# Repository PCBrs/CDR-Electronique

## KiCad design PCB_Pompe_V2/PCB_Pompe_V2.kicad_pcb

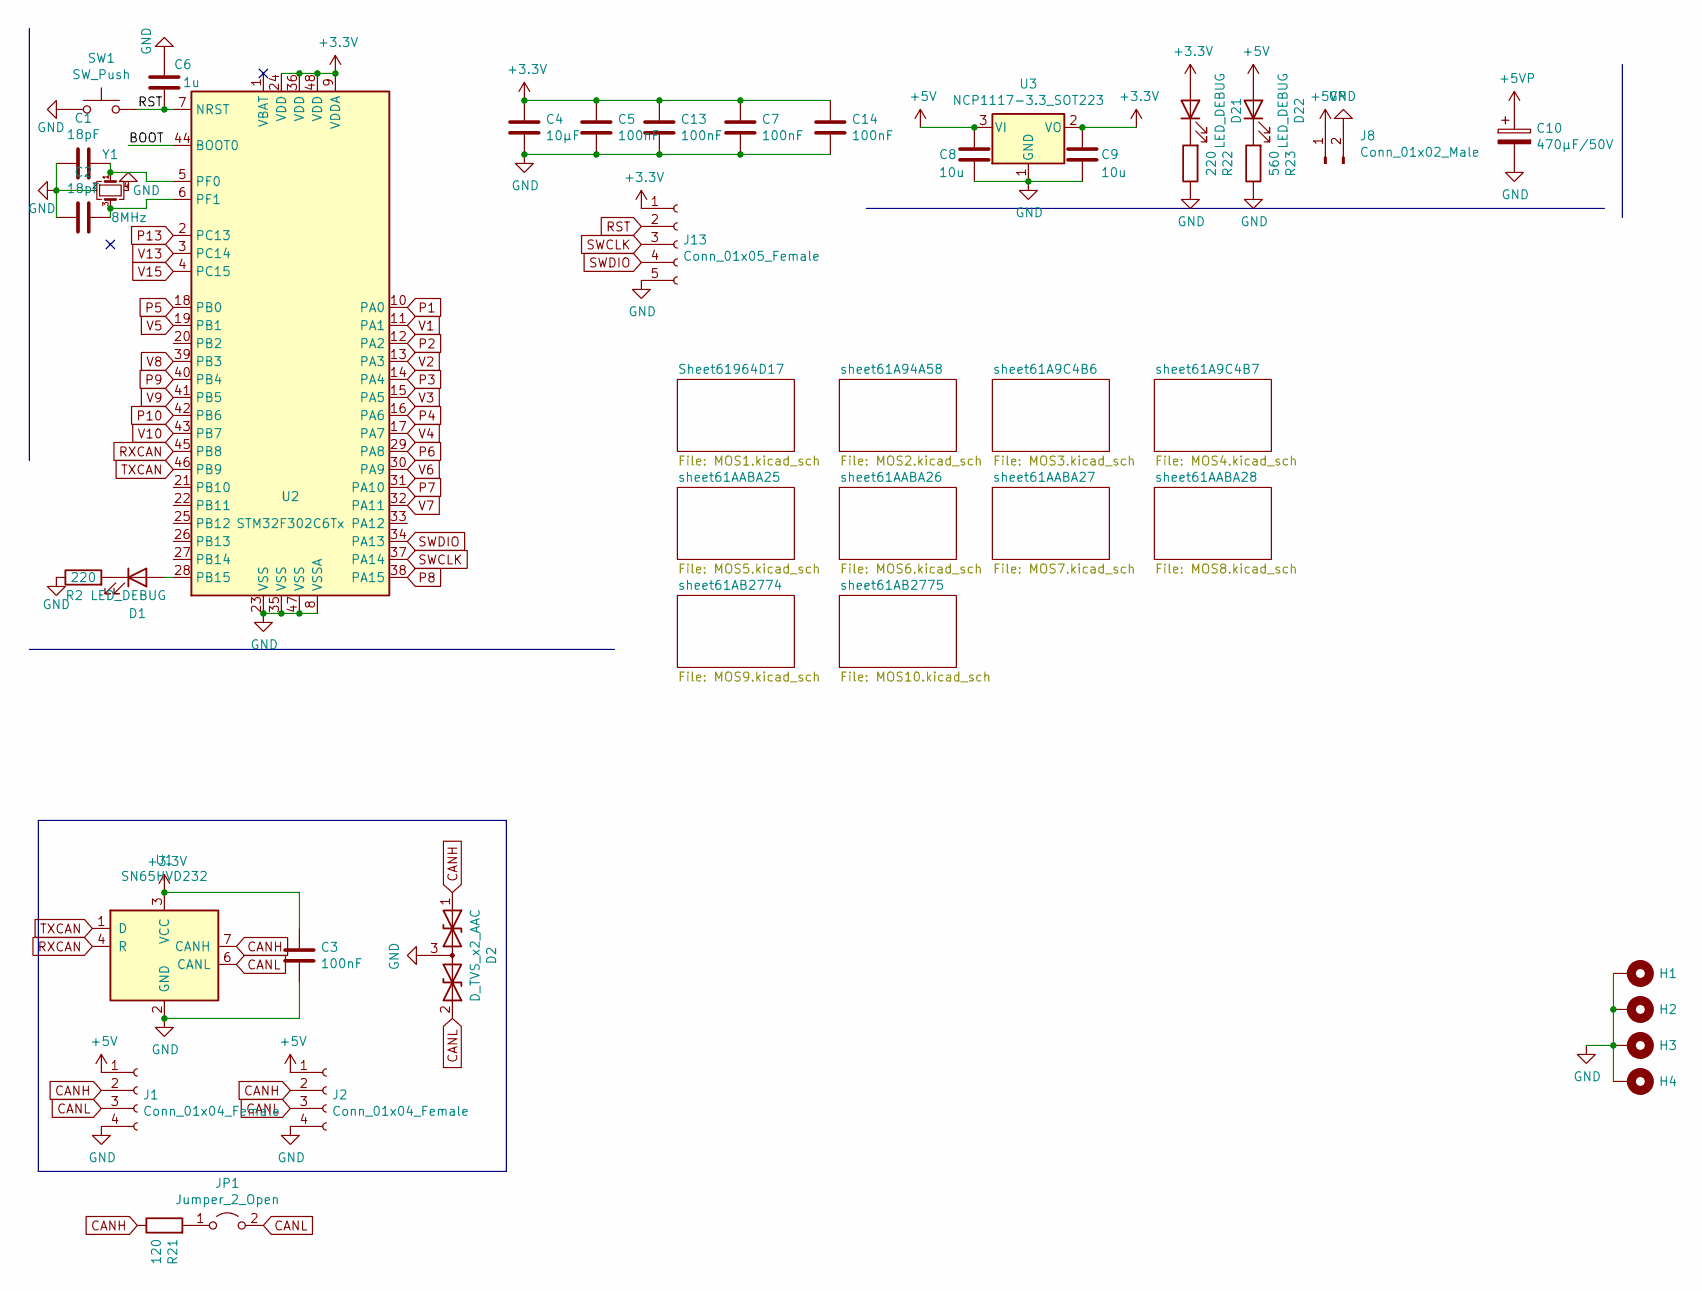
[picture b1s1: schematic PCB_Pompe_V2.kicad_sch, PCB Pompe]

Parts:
C1, C2: 18pF; C_0805_2012Metric_Pad1.18x1.45mm_HandSolder
C3, C5, C7, C13, C14: 100nF; C_0805_2012Metric_Pad1.18x1.45mm_HandSolder
C4: 10µF; C_0805_2012Metric_Pad1.18x1.45mm_HandSolder
C6: 1u; C_0805_2012Metric_Pad1.18x1.45mm_HandSolder
C8, C9: 10u; C_0805_2012Metric_Pad1.18x1.45mm_HandSolder
C10: 470µF/50V; CP_Radial_D10.0mm_P5.00mm
D1, D21, D22: LED_DEBUG; LED_0805_2012Metric_Pad1.15x1.40mm_HandSolder
D2: D_TVS_x2_AAC; SOT-23
H1, H2, H3, H4: MountingHole_Pad; MountingHole_3.2mm_M3_Pad_Via
J1, J2: Conn_01x04_Female; 690367290476
J8: Conn_01x02_Male; Wuerth_3.96mm_2pin_645002114822
J13: Conn_01x05_Female; PinSocket_1x05_P2.54mm_Vertical
JP1: Jumper_2_Open; PinHeader_1x02_P2.54mm_Vertical
R2, R22: 220; R_0805_2012Metric_Pad1.20x1.40mm_HandSolder
R21: 120; R_0805_2012Metric_Pad1.20x1.40mm_HandSolder
R23: 560; R_0805_2012Metric_Pad1.20x1.40mm_HandSolder
SW1: SW_Push; SW_SPST_FSMSM
U1: SN65HVD232; SOIC-8_3.9x4.9mm_P1.27mm
U2: STM32F302C6Tx; LQFP-48_7x7mm_P0.5mm
U3: NCP1117-3.3_SOT223; SOT-223-3_TabPin2
Y1: 8MHz; Crystal_SMD_5032-4Pin_5.0x3.2mm

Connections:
+3V3: C3.2, C4.2, C5.2, C7.2, C9.2, C13.2, C14.2, D21.2 (A), J13.1, U1.3 (VCC), U2.9 (VDDA), U2.24 (VDD), U2.36 (VDD), U2.48 (VDD), U3.2 (VO)
+5V: C8.2, D22.2 (A), J1.1, J2.1, U3.3 (VI)
+5VP: C10.1, J8.1; also elsewhere on the board
CANH: D2.1 (A1), J1.2, J2.2, R21.1, U1.7 (CANH)
CANL: D2.2 (A2), J1.3, J2.3, JP1.2 (B), U1.6 (CANL)
GND: C1.2, C2.2, C3.1, C4.1, C5.1, C6.2, C7.1, C8.1, C9.1, C10.2, C13.1, C14.1, D2.3 (common), H1.1, H2.1, H3.1, H4.1, J1.4, J2.4, J8.2, J13.5, R2.1, R22.1, R23.1, SW1.1, U1.2 (GND), U2.8 (VSSA), U2.23 (VSS), U2.35 (VSS), U2.47 (VSS), U3.1 (GND), Y1.2, Y1.4; also elsewhere on the board
unnamed: C1.1, U2.5 (PF0), Y1.1
unnamed: C2.1, U2.6 (PF1), Y1.3
unnamed: D1.1 (K), R2.2
unnamed: D1.2 (A), U2.28 (PB15)
unnamed: D21.1 (K), R22.2
unnamed: D22.1 (K), R23.2
unnamed: JP1.1 (A), R21.2
P1: U2.10 (PA0); also elsewhere on the board
P2: U2.12 (PA2); also elsewhere on the board
P3: U2.14 (PA4); also elsewhere on the board
P4: U2.16 (PA6); also elsewhere on the board
P5: U2.18 (PB0); also elsewhere on the board
P6: U2.29 (PA8); also elsewhere on the board
P7: U2.31 (PA10); also elsewhere on the board
P8: U2.38 (PA15); also elsewhere on the board
P9: U2.40 (PB4); also elsewhere on the board
P10: U2.42 (PB6); also elsewhere on the board
RST: C6.1, J13.2, SW1.2, U2.7 (NRST)
RXCAN: U1.4 (R), U2.45 (PB8)
SWCLK: J13.3, U2.37 (PA14)
SWDIO: J13.4, U2.34 (PA13)
TXCAN: U1.1 (D), U2.46 (PB9)
V1: U2.11 (PA1); also elsewhere on the board
V2: U2.13 (PA3); also elsewhere on the board
V3: U2.15 (PA5); also elsewhere on the board
V4: U2.17 (PA7); also elsewhere on the board
V5: U2.19 (PB1); also elsewhere on the board
V6: U2.30 (PA9); also elsewhere on the board
V7: U2.32 (PA11); also elsewhere on the board
V8: U2.39 (PB3); also elsewhere on the board
V9: U2.41 (PB5); also elsewhere on the board
V10: U2.43 (PB7); also elsewhere on the board

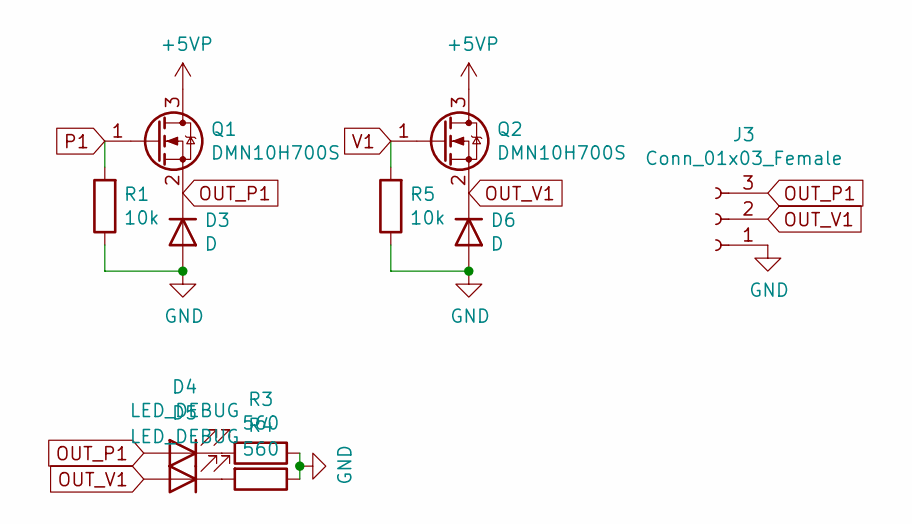
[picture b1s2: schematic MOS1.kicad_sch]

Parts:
D3, D6: D; D_SOD-123
D4, D5: LED_DEBUG; LED_0805_2012Metric_Pad1.15x1.40mm_HandSolder
J3: Conn_01x03_Female; Wuerth_2.54mm_3pins_61900311121
Q1, Q2: DMN10H700S; SOT-23
R1, R5: 10k; R_0805_2012Metric_Pad1.20x1.40mm_HandSolder
R3, R4: 560; R_0805_2012Metric_Pad1.20x1.40mm_HandSolder

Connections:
+5VP: Q1.3 (D), Q2.3 (D); also elsewhere on the board
GND: D3.2 (A), D6.2 (A), J3.1, R1.1, R3.1, R4.1, R5.1; also elsewhere on the board
unnamed: D4.1 (K), R3.2
unnamed: D5.1 (K), R4.2
OUT_P1: D3.1 (K), D4.2 (A), J3.3, Q1.2 (S)
OUT_V1: D5.2 (A), D6.1 (K), J3.2, Q2.2 (S)
P1: Q1.1 (G), R1.2; also elsewhere on the board
V1: Q2.1 (G), R5.2; also elsewhere on the board

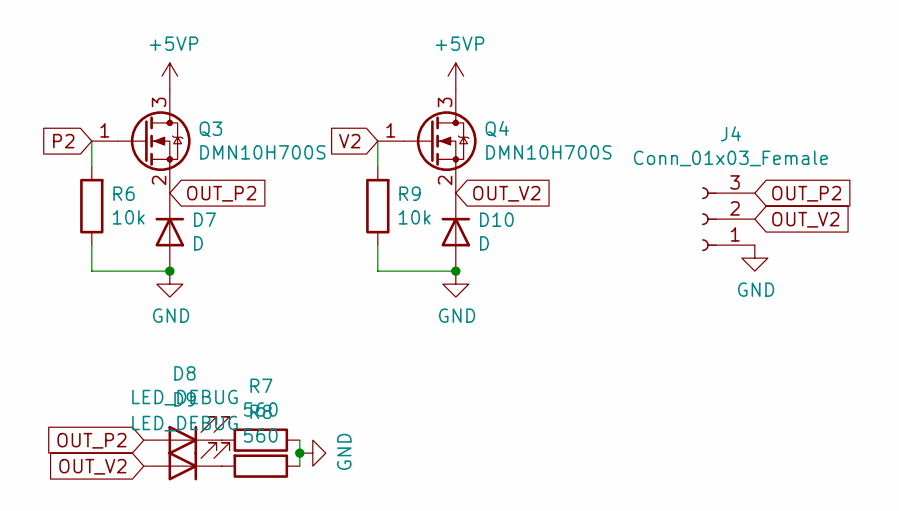
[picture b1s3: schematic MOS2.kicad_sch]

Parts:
D7, D10: D; D_SOD-123
D8, D9: LED_DEBUG; LED_0805_2012Metric_Pad1.15x1.40mm_HandSolder
J4: Conn_01x03_Female; Wuerth_2.54mm_3pins_61900311121
Q3, Q4: DMN10H700S; SOT-23
R6, R9: 10k; R_0805_2012Metric_Pad1.20x1.40mm_HandSolder
R7, R8: 560; R_0805_2012Metric_Pad1.20x1.40mm_HandSolder

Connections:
+5VP: Q3.3 (D), Q4.3 (D); also elsewhere on the board
GND: D7.2 (A), D10.2 (A), J4.1, R6.1, R7.1, R8.1, R9.1; also elsewhere on the board
unnamed: D8.1 (K), R7.2
unnamed: D9.1 (K), R8.2
OUT_P2: D7.1 (K), D8.2 (A), J4.3, Q3.2 (S)
OUT_V2: D9.2 (A), D10.1 (K), J4.2, Q4.2 (S)
P2: Q3.1 (G), R6.2; also elsewhere on the board
V2: Q4.1 (G), R9.2; also elsewhere on the board

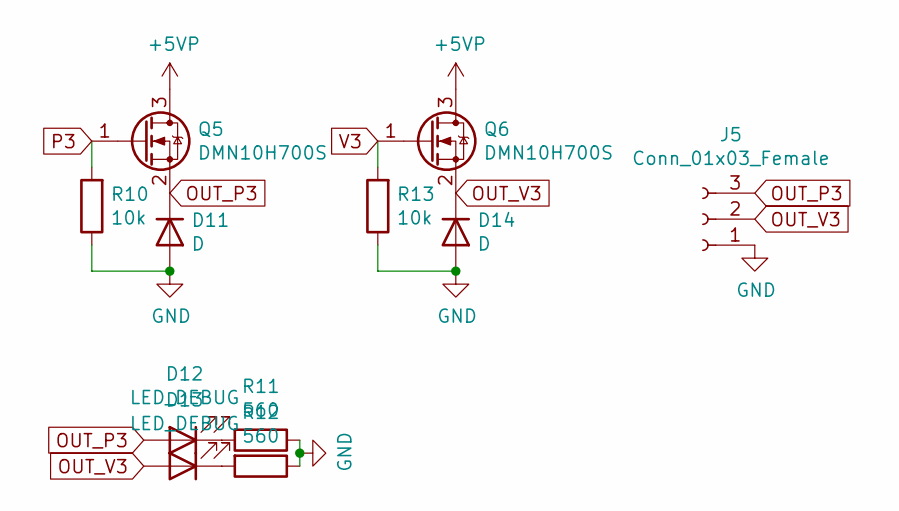
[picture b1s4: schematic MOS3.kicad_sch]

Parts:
D11, D14: D; D_SOD-123
D12, D13: LED_DEBUG; LED_0805_2012Metric_Pad1.15x1.40mm_HandSolder
J5: Conn_01x03_Female; Wuerth_2.54mm_3pins_61900311121
Q5, Q6: DMN10H700S; SOT-23
R10, R13: 10k; R_0805_2012Metric_Pad1.20x1.40mm_HandSolder
R11, R12: 560; R_0805_2012Metric_Pad1.20x1.40mm_HandSolder

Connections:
+5VP: Q5.3 (D), Q6.3 (D); also elsewhere on the board
GND: D11.2 (A), D14.2 (A), J5.1, R10.1, R11.1, R12.1, R13.1; also elsewhere on the board
unnamed: D12.1 (K), R11.2
unnamed: D13.1 (K), R12.2
OUT_P3: D11.1 (K), D12.2 (A), J5.3, Q5.2 (S)
OUT_V3: D13.2 (A), D14.1 (K), J5.2, Q6.2 (S)
P3: Q5.1 (G), R10.2; also elsewhere on the board
V3: Q6.1 (G), R13.2; also elsewhere on the board

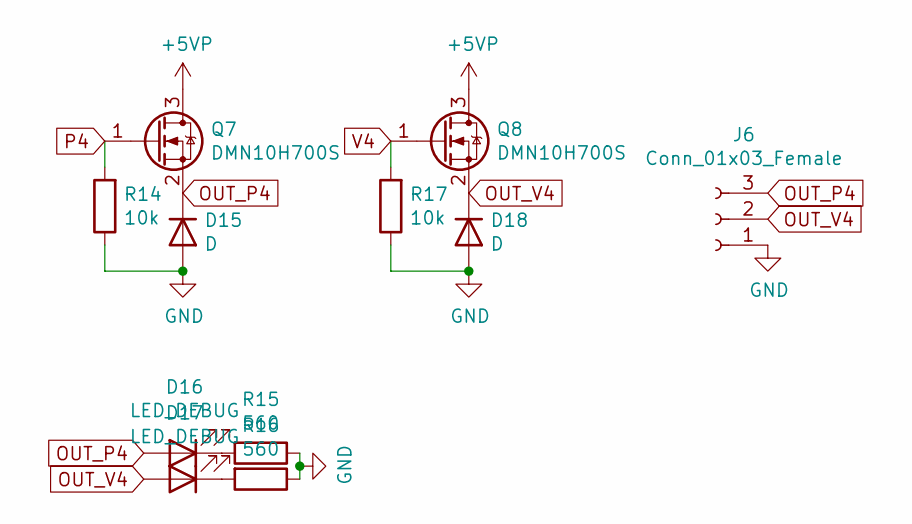
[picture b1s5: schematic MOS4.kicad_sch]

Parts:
D15, D18: D; D_SOD-123
D16, D17: LED_DEBUG; LED_0805_2012Metric_Pad1.15x1.40mm_HandSolder
J6: Conn_01x03_Female; Wuerth_2.54mm_3pins_61900311121
Q7, Q8: DMN10H700S; SOT-23
R14, R17: 10k; R_0805_2012Metric_Pad1.20x1.40mm_HandSolder
R15, R16: 560; R_0805_2012Metric_Pad1.20x1.40mm_HandSolder

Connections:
+5VP: Q7.3 (D), Q8.3 (D); also elsewhere on the board
GND: D15.2 (A), D18.2 (A), J6.1, R14.1, R15.1, R16.1, R17.1; also elsewhere on the board
unnamed: D16.1 (K), R15.2
unnamed: D17.1 (K), R16.2
OUT_P4: D15.1 (K), D16.2 (A), J6.3, Q7.2 (S)
OUT_V4: D17.2 (A), D18.1 (K), J6.2, Q8.2 (S)
P4: Q7.1 (G), R14.2; also elsewhere on the board
V4: Q8.1 (G), R17.2; also elsewhere on the board

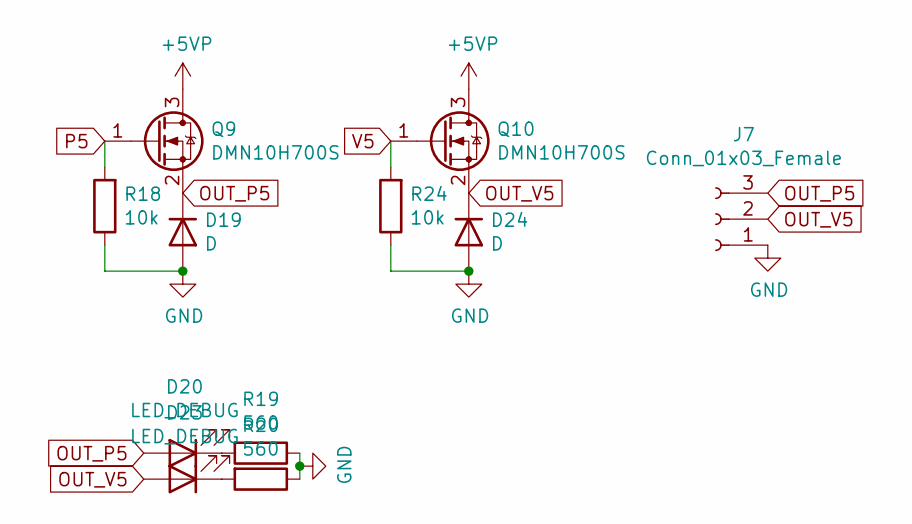
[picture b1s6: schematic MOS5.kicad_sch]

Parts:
D19, D24: D; D_SOD-123
D20, D23: LED_DEBUG; LED_0805_2012Metric_Pad1.15x1.40mm_HandSolder
J7: Conn_01x03_Female; Wuerth_2.54mm_3pins_61900311121
Q9, Q10: DMN10H700S; SOT-23
R18, R24: 10k; R_0805_2012Metric_Pad1.20x1.40mm_HandSolder
R19, R20: 560; R_0805_2012Metric_Pad1.20x1.40mm_HandSolder

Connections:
+5VP: Q9.3 (D), Q10.3 (D); also elsewhere on the board
GND: D19.2 (A), D24.2 (A), J7.1, R18.1, R19.1, R20.1, R24.1; also elsewhere on the board
unnamed: D20.1 (K), R19.2
unnamed: D23.1 (K), R20.2
OUT_P5: D19.1 (K), D20.2 (A), J7.3, Q9.2 (S)
OUT_V5: D23.2 (A), D24.1 (K), J7.2, Q10.2 (S)
P5: Q9.1 (G), R18.2; also elsewhere on the board
V5: Q10.1 (G), R24.2; also elsewhere on the board

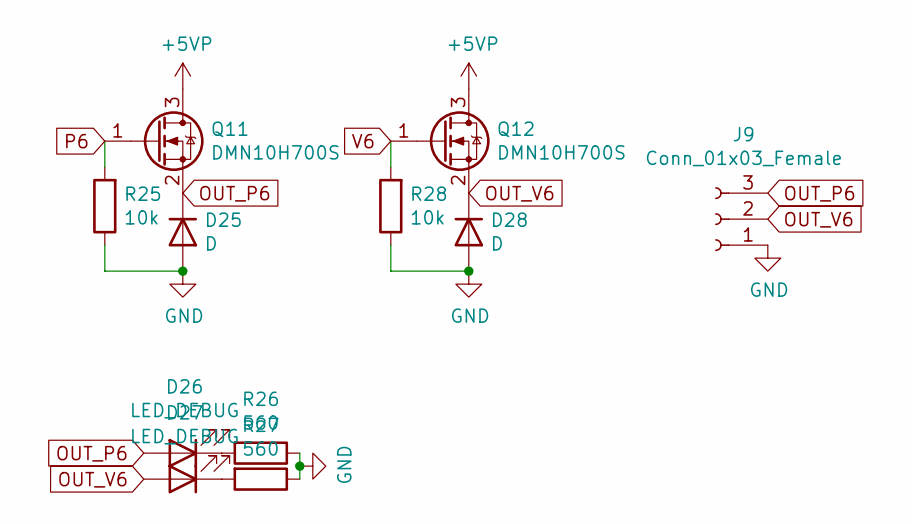
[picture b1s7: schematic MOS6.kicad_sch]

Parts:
D25, D28: D; D_SOD-123
D26, D27: LED_DEBUG; LED_0805_2012Metric_Pad1.15x1.40mm_HandSolder
J9: Conn_01x03_Female; Wuerth_2.54mm_3pins_61900311121
Q11, Q12: DMN10H700S; SOT-23
R25, R28: 10k; R_0805_2012Metric_Pad1.20x1.40mm_HandSolder
R26, R27: 560; R_0805_2012Metric_Pad1.20x1.40mm_HandSolder

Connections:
+5VP: Q11.3 (D), Q12.3 (D); also elsewhere on the board
GND: D25.2 (A), D28.2 (A), J9.1, R25.1, R26.1, R27.1, R28.1; also elsewhere on the board
unnamed: D26.1 (K), R26.2
unnamed: D27.1 (K), R27.2
OUT_P6: D25.1 (K), D26.2 (A), J9.3, Q11.2 (S)
OUT_V6: D27.2 (A), D28.1 (K), J9.2, Q12.2 (S)
P6: Q11.1 (G), R25.2; also elsewhere on the board
V6: Q12.1 (G), R28.2; also elsewhere on the board

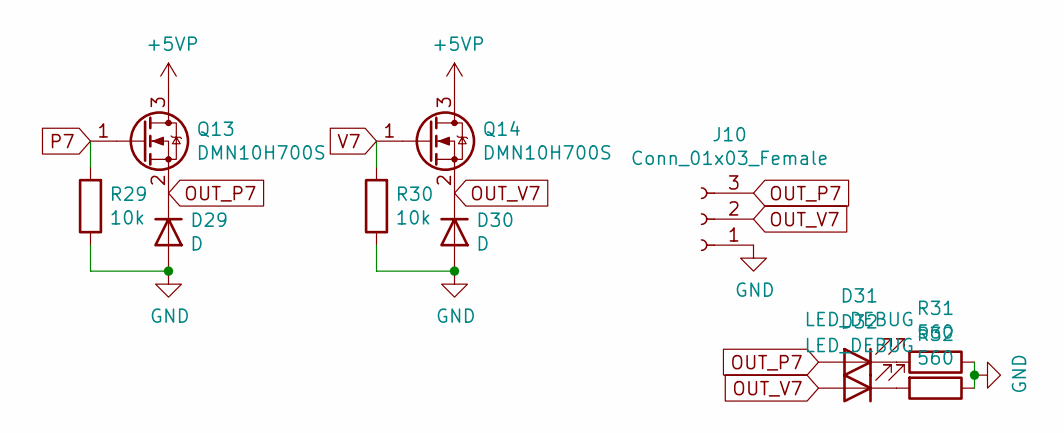
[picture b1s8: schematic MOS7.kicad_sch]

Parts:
D29, D30: D; D_SOD-123
D31, D32: LED_DEBUG; LED_0805_2012Metric_Pad1.15x1.40mm_HandSolder
J10: Conn_01x03_Female; Wuerth_2.54mm_3pins_61900311121
Q13, Q14: DMN10H700S; SOT-23
R29, R30: 10k; R_0805_2012Metric_Pad1.20x1.40mm_HandSolder
R31, R32: 560; R_0805_2012Metric_Pad1.20x1.40mm_HandSolder

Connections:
+5VP: Q13.3 (D), Q14.3 (D); also elsewhere on the board
GND: D29.2 (A), D30.2 (A), J10.1, R29.1, R30.1, R31.1, R32.1; also elsewhere on the board
unnamed: D31.1 (K), R31.2
unnamed: D32.1 (K), R32.2
OUT_P7: D29.1 (K), D31.2 (A), J10.3, Q13.2 (S)
OUT_V7: D30.1 (K), D32.2 (A), J10.2, Q14.2 (S)
P7: Q13.1 (G), R29.2; also elsewhere on the board
V7: Q14.1 (G), R30.2; also elsewhere on the board

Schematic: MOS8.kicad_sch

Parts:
D33, D36: D; D_SOD-123
D34, D35: LED_DEBUG; LED_0805_2012Metric_Pad1.15x1.40mm_HandSolder
J11: Conn_01x03_Female; Wuerth_2.54mm_3pins_61900311121
Q15, Q16: DMN10H700S; SOT-23
R33, R36: 10k; R_0805_2012Metric_Pad1.20x1.40mm_HandSolder
R34, R35: 560; R_0805_2012Metric_Pad1.20x1.40mm_HandSolder

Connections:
+5VP: Q15.3 (D), Q16.3 (D); also elsewhere on the board
GND: D33.2 (A), D36.2 (A), J11.1, R33.1, R34.1, R35.1, R36.1; also elsewhere on the board
unnamed: D34.1 (K), R34.2
unnamed: D35.1 (K), R35.2
OUT_P8: D33.1 (K), D34.2 (A), J11.3, Q15.2 (S)
OUT_V8: D35.2 (A), D36.1 (K), J11.2, Q16.2 (S)
P8: Q15.1 (G), R33.2; also elsewhere on the board
V8: Q16.1 (G), R36.2; also elsewhere on the board

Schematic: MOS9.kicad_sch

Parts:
D37, D40: D; D_SOD-123
D38, D39: LED_DEBUG; LED_0805_2012Metric_Pad1.15x1.40mm_HandSolder
J12: Conn_01x03_Female; Wuerth_2.54mm_3pins_61900311121
Q17, Q18: DMN10H700S; SOT-23
R37, R40: 10k; R_0805_2012Metric_Pad1.20x1.40mm_HandSolder
R38, R39: 560; R_0805_2012Metric_Pad1.20x1.40mm_HandSolder

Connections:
+5VP: Q17.3 (D), Q18.3 (D); also elsewhere on the board
GND: D37.2 (A), D40.2 (A), J12.1, R37.1, R38.1, R39.1, R40.1; also elsewhere on the board
unnamed: D38.1 (K), R38.2
unnamed: D39.1 (K), R39.2
OUT_P9: D37.1 (K), D38.2 (A), J12.3, Q17.2 (S)
OUT_V9: D39.2 (A), D40.1 (K), J12.2, Q18.2 (S)
P9: Q17.1 (G), R37.2; also elsewhere on the board
V9: Q18.1 (G), R40.2; also elsewhere on the board

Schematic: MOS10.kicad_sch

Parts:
D41, D44: D; D_SOD-123
D42, D43: LED_DEBUG; LED_0805_2012Metric_Pad1.15x1.40mm_HandSolder
J14: Conn_01x03_Female; Wuerth_2.54mm_3pins_61900311121
Q19, Q20: DMN10H700S; SOT-23
R41, R44: 10k; R_0805_2012Metric_Pad1.20x1.40mm_HandSolder
R42, R43: 560; R_0805_2012Metric_Pad1.20x1.40mm_HandSolder

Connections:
+5VP: Q19.3 (D), Q20.3 (D); also elsewhere on the board
GND: D41.2 (A), D44.2 (A), J14.1, R41.1, R42.1, R43.1, R44.1; also elsewhere on the board
unnamed: D42.1 (K), R42.2
unnamed: D43.1 (K), R43.2
OUT_P10: D41.1 (K), D42.2 (A), J14.3, Q19.2 (S)
OUT_V10: D43.2 (A), D44.1 (K), J14.2, Q20.2 (S)
P10: Q19.1 (G), R41.2; also elsewhere on the board
V10: Q20.1 (G), R44.2; also elsewhere on the board

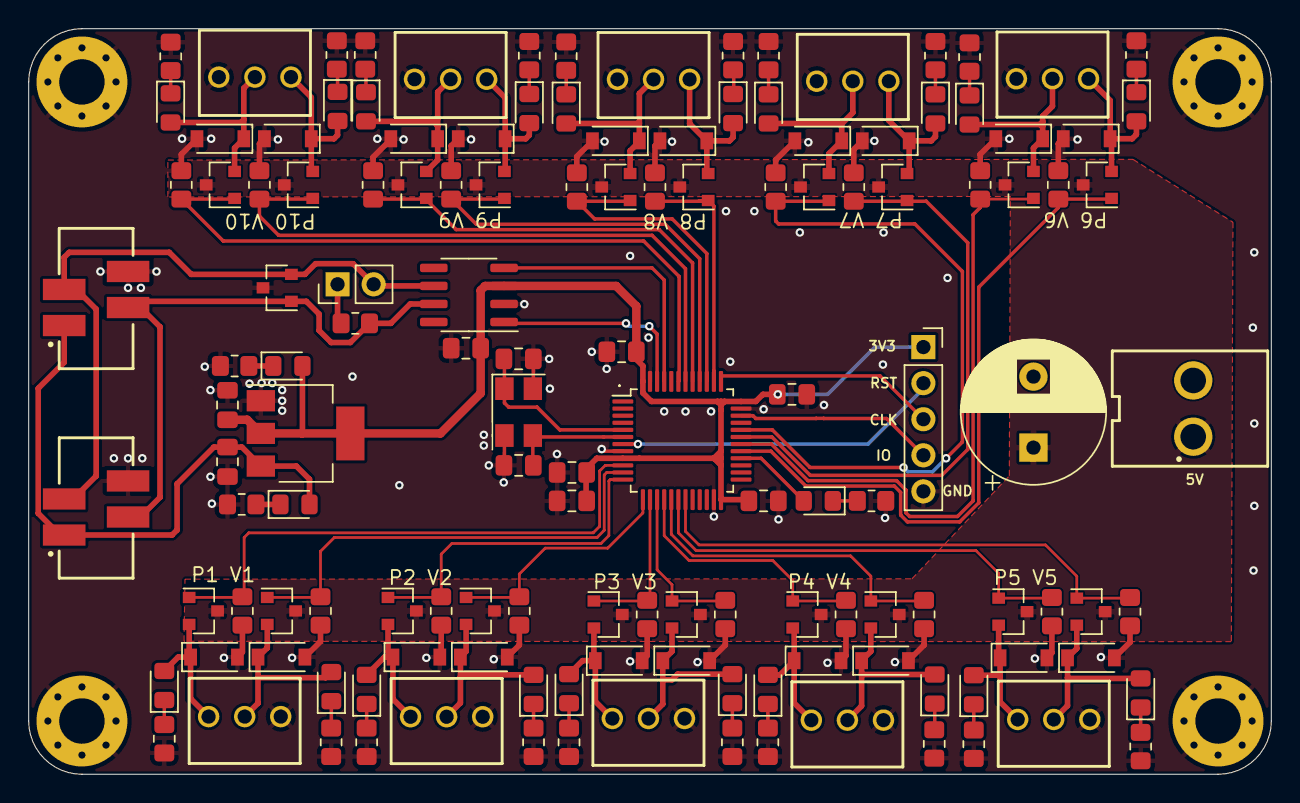
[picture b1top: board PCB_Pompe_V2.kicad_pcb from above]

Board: 2 copper layers, 87.5 x 52.5 mm, 142 parts (0 on the bottom side), 78 nets.

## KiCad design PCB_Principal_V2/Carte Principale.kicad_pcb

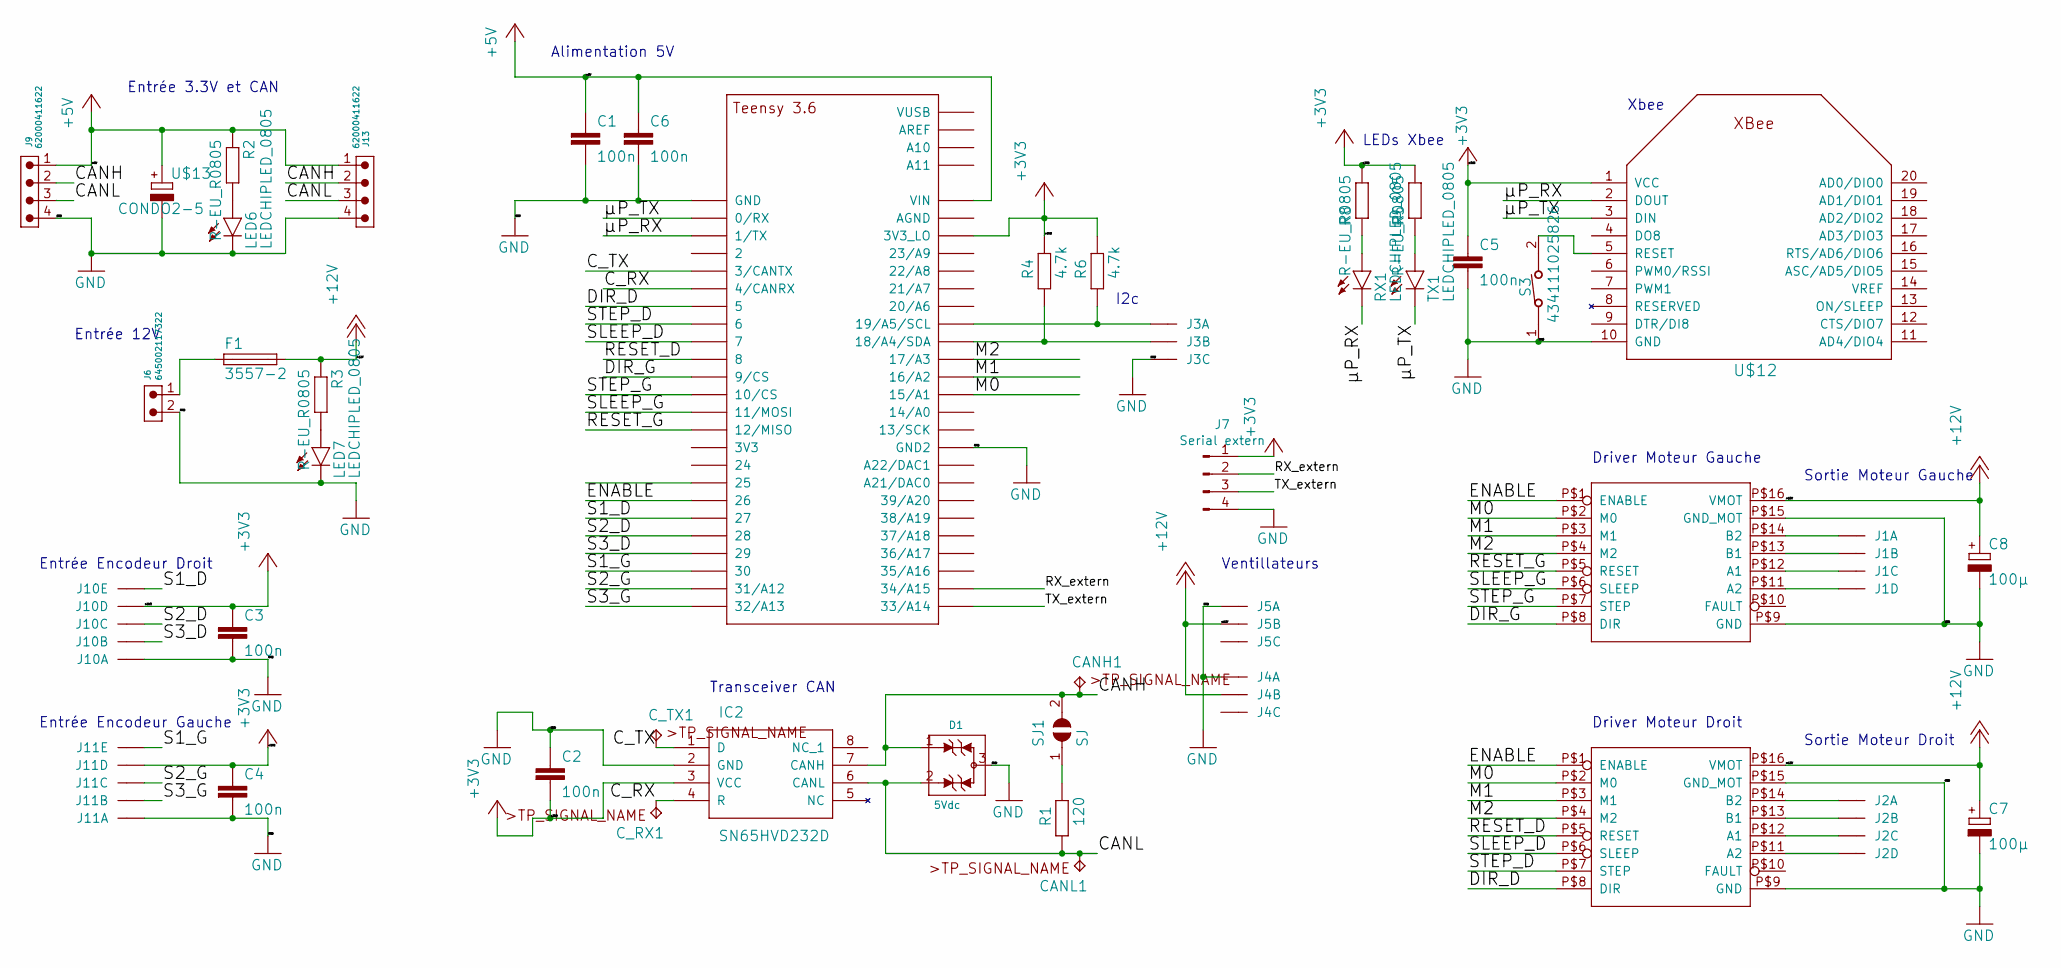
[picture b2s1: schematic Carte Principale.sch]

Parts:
C1, C2, C3, C4, C5, C6: 100n; C0805; MPN DT000363
C7, C8: 100µ; E2,5-7
CANH1: TPB1,27; B1,27
CANL1: TPB1,27; B1,27
C_RX1: TPB1,27; B1,27
C_TX1: TPB1,27; B1,27
D1: 5Vdc; WE-TVS_SOT23-3L
F1: 3557-2; FUSE_3557-2
IC2: SN65HVD232D; SOIC127P600X175-8N
J1, J2: MOLEX_4DROIT; CON_4_DROIT
J3, J4, J5: MOLEX_3DROIT; CON_3_DROIT
J6: 645002117322
J7: Serial extern; PinHeader_1x04_P2.54mm_Vertical
J9, J13: 62000411622
J10, J11: 22-?-0527-2051; 6410-05
LED6, LED7: LEDCHIPLED_0805; CHIPLED_0805
R1: 120; R0805
R2, R3, R5, R8: R-EU_R0805; R0805
R4, R6: 4.7k; R0805
RX1: LEDCHIPLED_0805; CHIPLED_0805
S3: 434111025826
SJ1: SJ
TX1: LEDCHIPLED_0805; CHIPLED_0805
U$1, U$2: DRV8825
U$5: TEENSY_3.5_3.6_BASIC
U$12: XBEE
U$13: CONDO2-5; E2-5

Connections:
+3V3: C2.2, C3.1, C4.1, C5.1, IC2.3 (VCC), J7.1, J10.4, J11.4, R4.2, R5.1, R6.2, R8.1, U$5.3V3_LO, U$12.1 (VCC)
+5V: C1.1, C6.1, J9.1, J13.1, R2.1, U$5.VIN, U$13.+
+12V: C7.+, C8.+, F1.3 (2), F1.4 (2), J4.2, J5.2, R3.1, U$1.P$16 (VMOT), U$2.P$16 (VMOT)
/CANH: CANH1.TP, D1.1 (I/O1), IC2.7 (CANH), J9.2, J13.2, SJ1.2
/CANL: CANL1.TP, D1.2 (I/O2), IC2.6 (CANL), J9.3, J13.3, R1.1
/C_RX: C_RX1.TP, IC2.4 (R), U$5.4/CANRX
/C_TX: C_TX1.TP, IC2.1 (D), U$5.3/CANTX
/DIR_D: U$2.P$8 (DIR), U$5.5
/DIR_G: U$1.P$8 (DIR), U$5.9/CS
/ENABLE: U$1.P$1 (ENABLE), U$2.P$1 (ENABLE), U$5.26
/M0: U$1.P$2 (M0), U$2.P$2 (M0), U$5.15/A1
/M1: U$1.P$3 (M1), U$2.P$3 (M1), U$5.16/A2
/M2: U$1.P$4 (M2), U$2.P$4 (M2), U$5.17/A3
/RESET_D: U$2.P$5 (RESET), U$5.8
/RESET_G: U$1.P$5 (RESET), U$5.12/MISO
/RX_extern: J7.2, U$5.34/A15
/S1_D: J10.5, U$5.27
/S1_G: J11.5, U$5.30
/S2_D: J10.3, U$5.28
/S2_G: J11.3, U$5.31/A12
/S3_D: J10.2, U$5.29
/S3_G: J11.2, U$5.32/A13
/SLEEP_D: U$2.P$6 (SLEEP), U$5.7
/SLEEP_G: U$1.P$6 (SLEEP), U$5.11/MOSI
/STEP_D: U$2.P$7 (STEP), U$5.6
/STEP_G: U$1.P$7 (STEP), U$5.10/CS
/TX_extern: J7.3, U$5.33/A14
/µP_RX: RX1.C, U$5.1/TX, U$12.2 (DOUT)
/µP_TX: TX1.C, U$5.0/RX, U$12.3 (DIN)
GND: C1.2, C2.1, C3.2, C4.2, C5.2, C6.2, C7.-, C8.-, D1.3 (GND), IC2.2 (GND), J3.3, J4.1, J5.1, J6.2, J7.4, J9.4, J10.1, J11.1, J13.4, LED6.C, LED7.C, S3.1, U$1.P$9 (GND), U$1.P$15 (GND_MOT), U$2.P$9 (GND), U$2.P$15 (GND_MOT), U$5.GND, U$5.GND2, U$12.10 (GND), U$13.-
unnamed: F1.1, F1.2 (1), J6.1
unnamed: J1.1, U$1.P$14 (B2)
unnamed: J1.2, U$1.P$13 (B1)
unnamed: J1.3, U$1.P$12 (A1)
unnamed: J1.4, U$1.P$11 (A2)
unnamed: J2.1, U$2.P$14 (B2)
unnamed: J2.2, U$2.P$13 (B1)
unnamed: J2.3, U$2.P$12 (A1)
unnamed: J2.4, U$2.P$11 (A2)
unnamed: J3.1, R6.1, U$5.19/A5/SCL
unnamed: J3.2, R4.1, U$5.18/A4/SDA
unnamed: LED6.A, R2.2
unnamed: LED7.A, R3.2
unnamed: R1.2, SJ1.1
unnamed: R5.2, TX1.A
unnamed: R8.2, RX1.A
unnamed: S3.2, U$12.5 (RESET)

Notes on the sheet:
Entrée Encodeur Gauche
Entrée Encodeur Droit
Sortie Moteur Gauche
Sortie Moteur Droit
Xbee
Driver Moteur Gauche
Driver Moteur Droit
Transceiver CAN
Entrée 12V
Entrée 3.3V et CAN
LEDs Xbee
I2c
Ventillateurs
Alimentation 5V

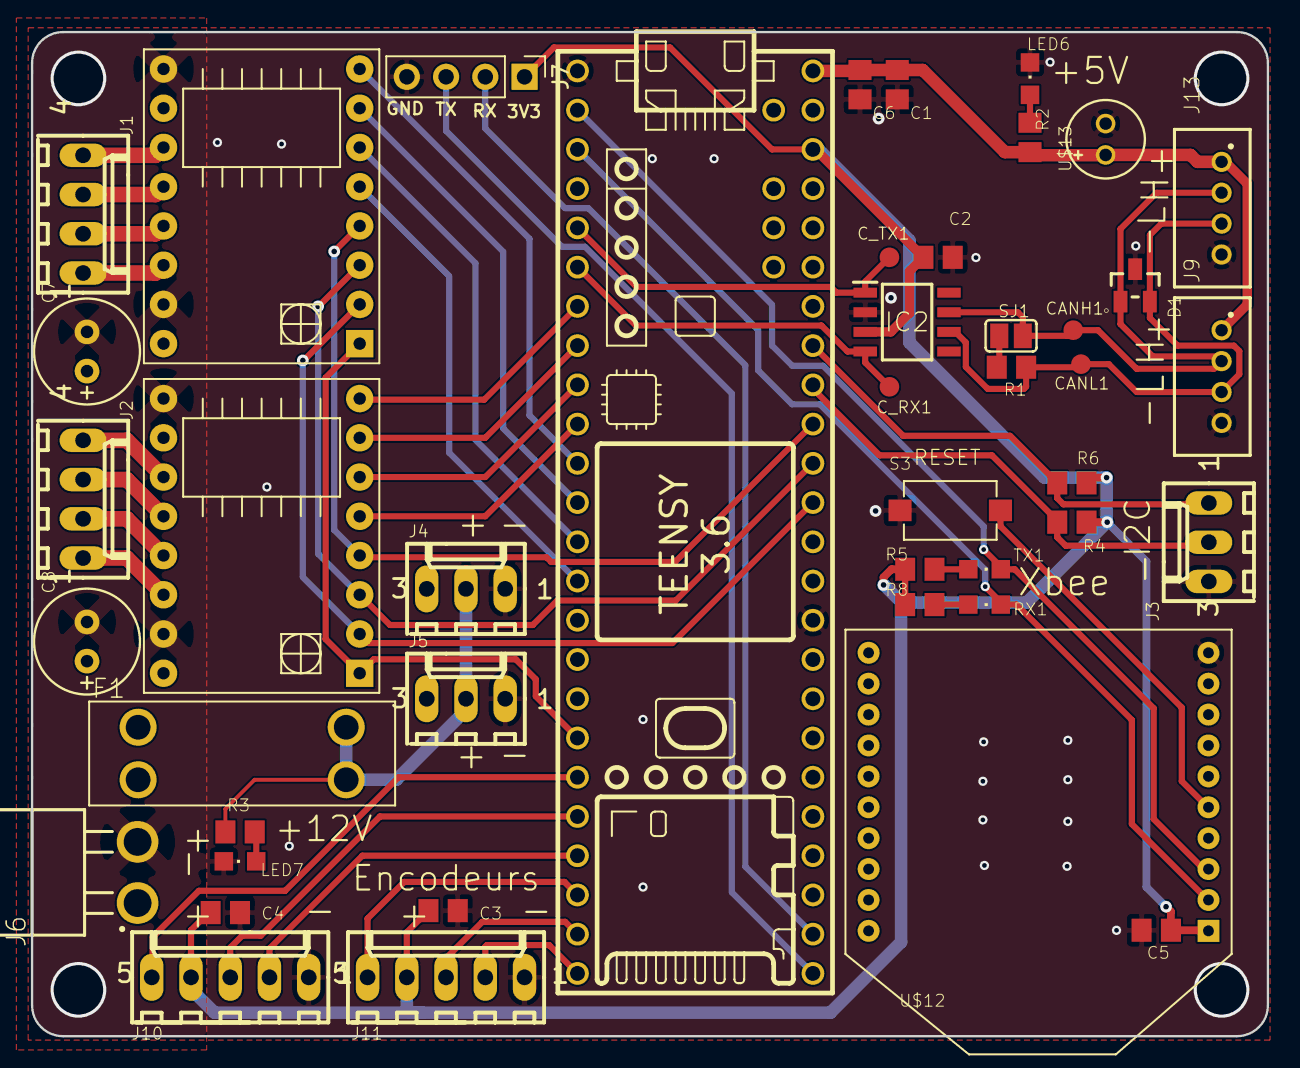
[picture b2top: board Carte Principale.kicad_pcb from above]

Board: 2 copper layers, 80.0 x 65.0 mm, 44 parts (0 on the bottom side), 47 nets.

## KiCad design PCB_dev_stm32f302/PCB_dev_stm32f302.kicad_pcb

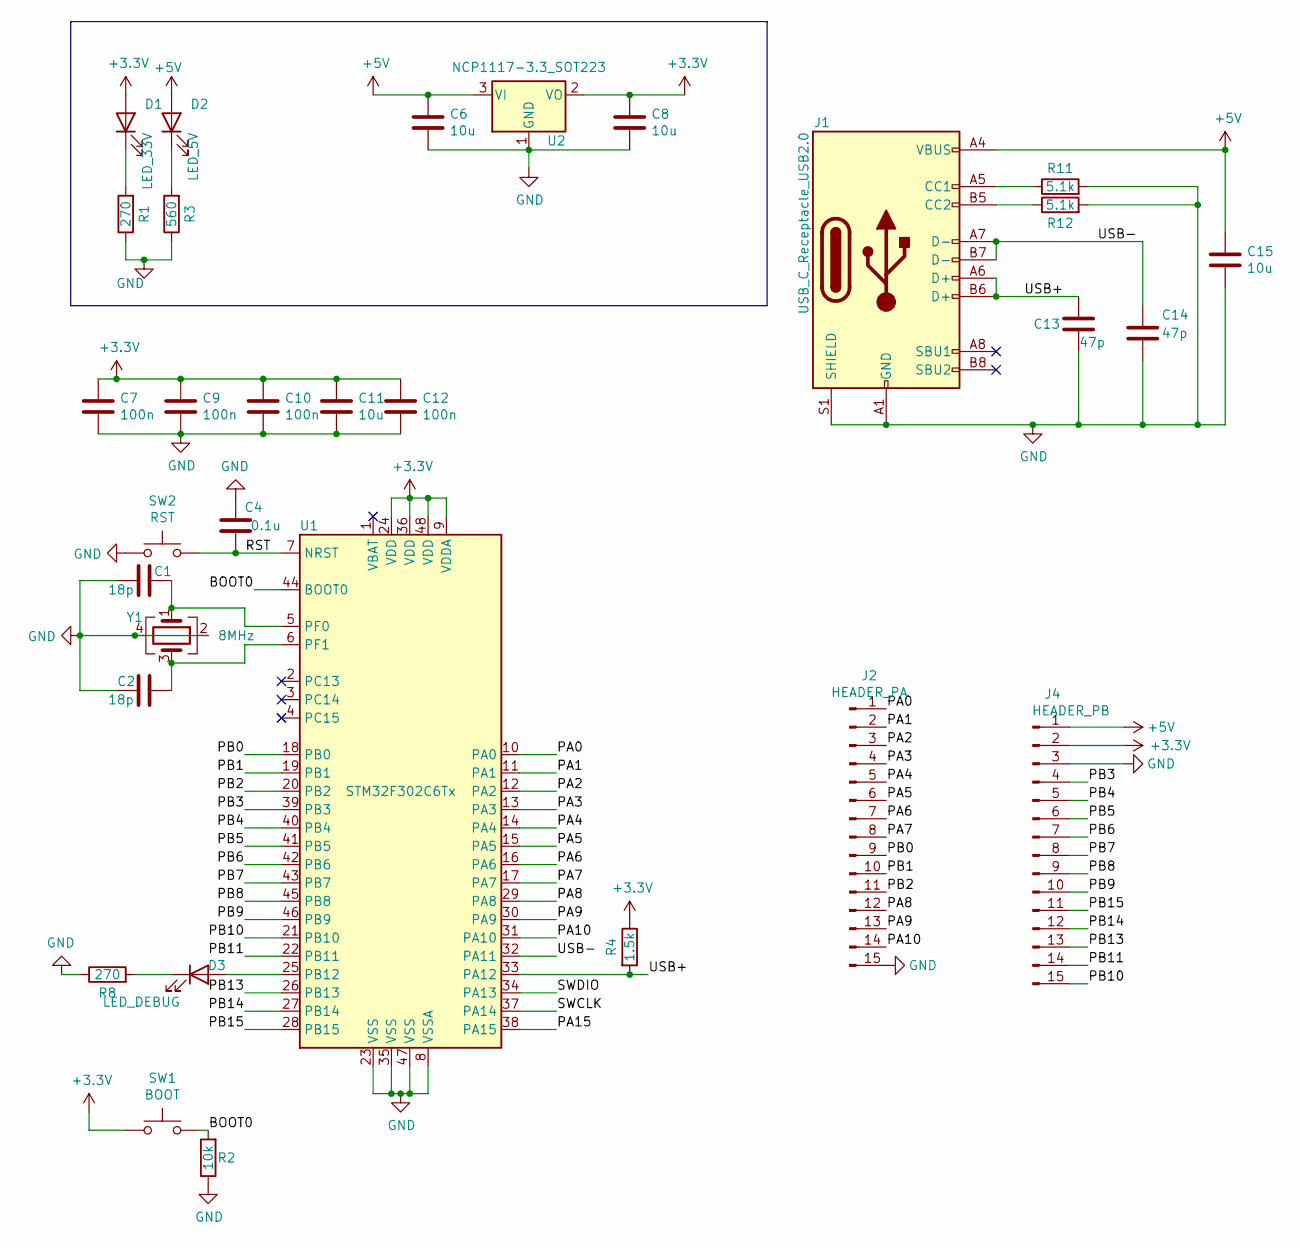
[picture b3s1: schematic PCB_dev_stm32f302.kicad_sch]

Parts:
C1, C2: 18p; C_0805_2012Metric_Pad1.18x1.45mm_HandSolder
C4: 0.1u; C_0805_2012Metric_Pad1.18x1.45mm_HandSolder
C6, C8, C11, C15: 10u; C_0805_2012Metric_Pad1.18x1.45mm_HandSolder
C7, C9, C10, C12: 100n; C_0805_2012Metric_Pad1.18x1.45mm_HandSolder
C13, C14: 47p; C_0805_2012Metric_Pad1.18x1.45mm_HandSolder
D1: LED_33V; LED_0805_2012Metric
D2: LED_5V; LED_0805_2012Metric
D3: LED_DEBUG; LED_0805_2012Metric
J1: USB_C_Receptacle_USB2.0; USB_C_Receptacle_GCT_USB4085
J2: HEADER_PA; PinHeader_1x15_P2.54mm_Vertical
J4: HEADER_PB; PinHeader_1x15_P2.54mm_Vertical
R1, R8: 270; R_0603_1608Metric_Pad0.98x0.95mm_HandSolder
R2: 10k; R_0603_1608Metric_Pad0.98x0.95mm_HandSolder
R3: 560; R_0603_1608Metric_Pad0.98x0.95mm_HandSolder
R4: 1.5k; R_0603_1608Metric_Pad0.98x0.95mm_HandSolder
R11, R12: 5.1k; R_0603_1608Metric_Pad0.98x0.95mm_HandSolder
SW1: BOOT; SW_SPST_CK_RS282G05A3
SW2: RST; SW_SPST_CK_RS282G05A3
U1: STM32F302C6Tx; LQFP-48_7x7mm_P0.5mm
U2: NCP1117-3.3_SOT223; SOT-223-3_TabPin2
Y1: 8MHz; Crystal_SMD_5032-4Pin_5.0x3.2mm

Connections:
+3V3: C7.1, C8.1, C9.1, C10.1, C11.1, C12.1, D1.2 (A), J4.2, R4.1, SW1.1, U1.9 (VDDA), U1.24 (VDD), U1.36 (VDD), U1.48 (VDD), U2.2 (VO)
+5V: C6.1, C15.1, D2.2 (A), J1.A4 (VBUS), J1.A9 (VBUS), J1.B4 (VBUS), J1.B9 (VBUS), J4.1, U2.3 (VI)
/BOOT0: R2.2, SW1.2, U1.44 (BOOT0)
/PA0: J2.1, U1.10 (PA0)
/PA1: J2.2, U1.11 (PA1)
/PA2: J2.3, U1.12 (PA2)
/PA3: J2.4, U1.13 (PA3)
/PA4: J2.5, U1.14 (PA4)
/PA5: J2.6, U1.15 (PA5)
/PA6: J2.7, U1.16 (PA6)
/PA7: J2.8, U1.17 (PA7)
/PA8: J2.12, U1.29 (PA8)
/PA9: J2.13, U1.30 (PA9)
/PA10: J2.14, U1.31 (PA10)
/PA15: U1.38 (PA15)
/PB0: J2.9, U1.18 (PB0)
/PB1: J2.10, U1.19 (PB1)
/PB2: J2.11, U1.20 (PB2)
/PB3: J4.4, U1.39 (PB3)
/PB4: J4.5, U1.40 (PB4)
/PB5: J4.6, U1.41 (PB5)
/PB6: J4.7, U1.42 (PB6)
/PB7: J4.8, U1.43 (PB7)
/PB8: J4.9, U1.45 (PB8)
/PB9: J4.10, U1.46 (PB9)
/PB10: J4.15, U1.21 (PB10)
/PB11: J4.14, U1.22 (PB11)
/PB13: J4.13, U1.26 (PB13)
/PB14: J4.12, U1.27 (PB14)
/PB15: J4.11, U1.28 (PB15)
/RST: C4.1, SW2.2, U1.7 (NRST)
/SWCLK: U1.37 (PA14)
/SWDIO: U1.34 (PA13)
/USB+: C13.1, J1.A6 (D+), J1.B6 (D+), R4.2, U1.33 (PA12)
/USB-: C14.1, J1.A7 (D-), J1.B7 (D-), U1.32 (PA11)
GND: C1.2, C2.2, C4.2, C6.2, C7.2, C8.2, C9.2, C10.2, C11.2, C12.2, C13.2, C14.2, C15.2, J1.A1 (GND), J1.A12 (GND), J1.B1 (GND), J1.B12 (GND), J1.S1 (SHIELD), J2.15, J4.3, R1.1, R2.1, R3.1, R8.1, R11.2, R12.2, SW2.1, U1.8 (VSSA), U1.23 (VSS), U1.35 (VSS), U1.47 (VSS), U2.1 (GND), Y1.2, Y1.4
unnamed: C1.1, U1.5 (PF0), Y1.1
unnamed: C2.1, U1.6 (PF1), Y1.3
unnamed: D1.1 (K), R1.2
unnamed: D2.1 (K), R3.2
unnamed: D3.1 (K), R8.2
unnamed: D3.2 (A), U1.25 (PB12)
unnamed: J1.A5 (CC1), R11.1
unnamed: J1.B5 (CC2), R12.1

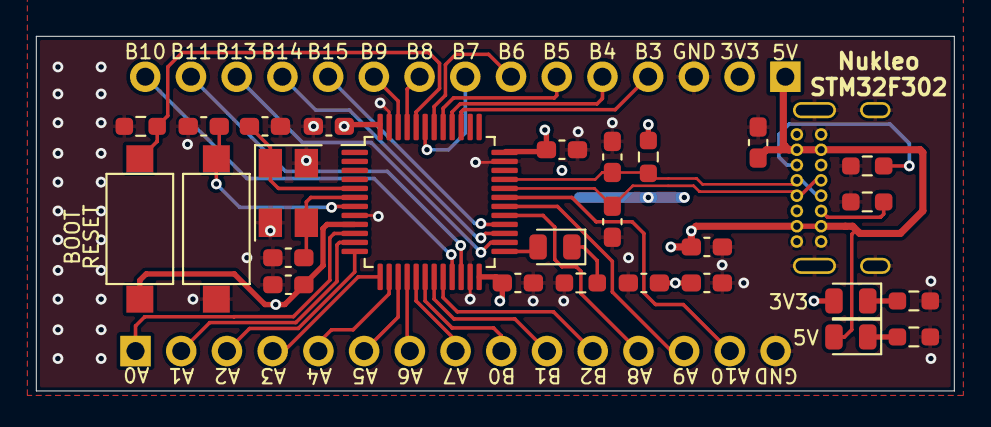
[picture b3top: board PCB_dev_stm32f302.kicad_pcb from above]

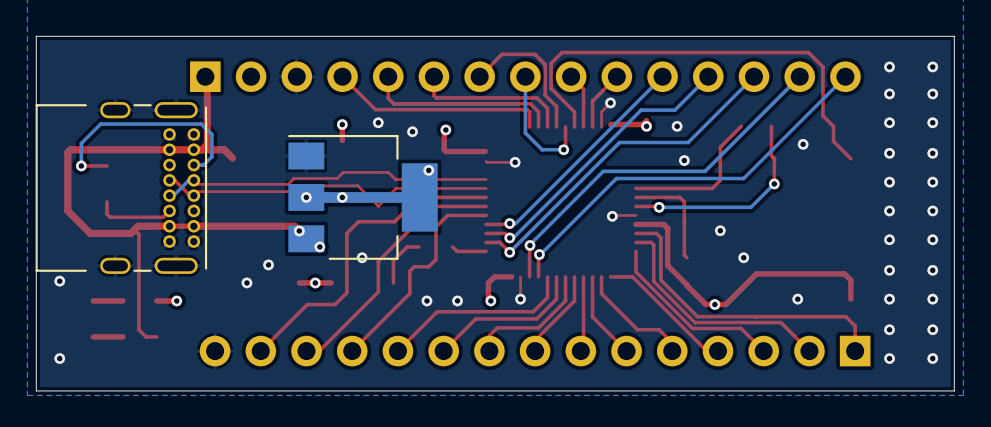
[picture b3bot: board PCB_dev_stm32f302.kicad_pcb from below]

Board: 4 copper layers, 51.0 x 19.7 mm, 31 parts (2 on the bottom side), 41 nets.
